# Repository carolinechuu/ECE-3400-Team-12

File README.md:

The home page is located in index.md, inside the master branch.

<!--
<div id="mySidenav" class="sidenav">
  <a href="javascript:void(0)" class="closebtn" onclick="closeNav()">&times;</a>
  <a href="#">About</a>
  <a href="#">Services</a>
  <a href="#">Clients</a>
  <a href="#">Contact</a>
</div> -->

<!--
<div class="w3-sidebar w3-bar-block" style="width:25%"> 
  <a href="#" class="w3-bar-item w3-button">Link 1</a>
  <a href="#" class="w3-bar-item w3-button">Link 2</a>
  <a href="#" class="w3-bar-item w3-button">Link 3</a>
</div>
-->

<!--<div style="margin-left:25%">-->

<!-- Use any element to open the sidenav 
<span onclick="openNav()">close</span>

-->

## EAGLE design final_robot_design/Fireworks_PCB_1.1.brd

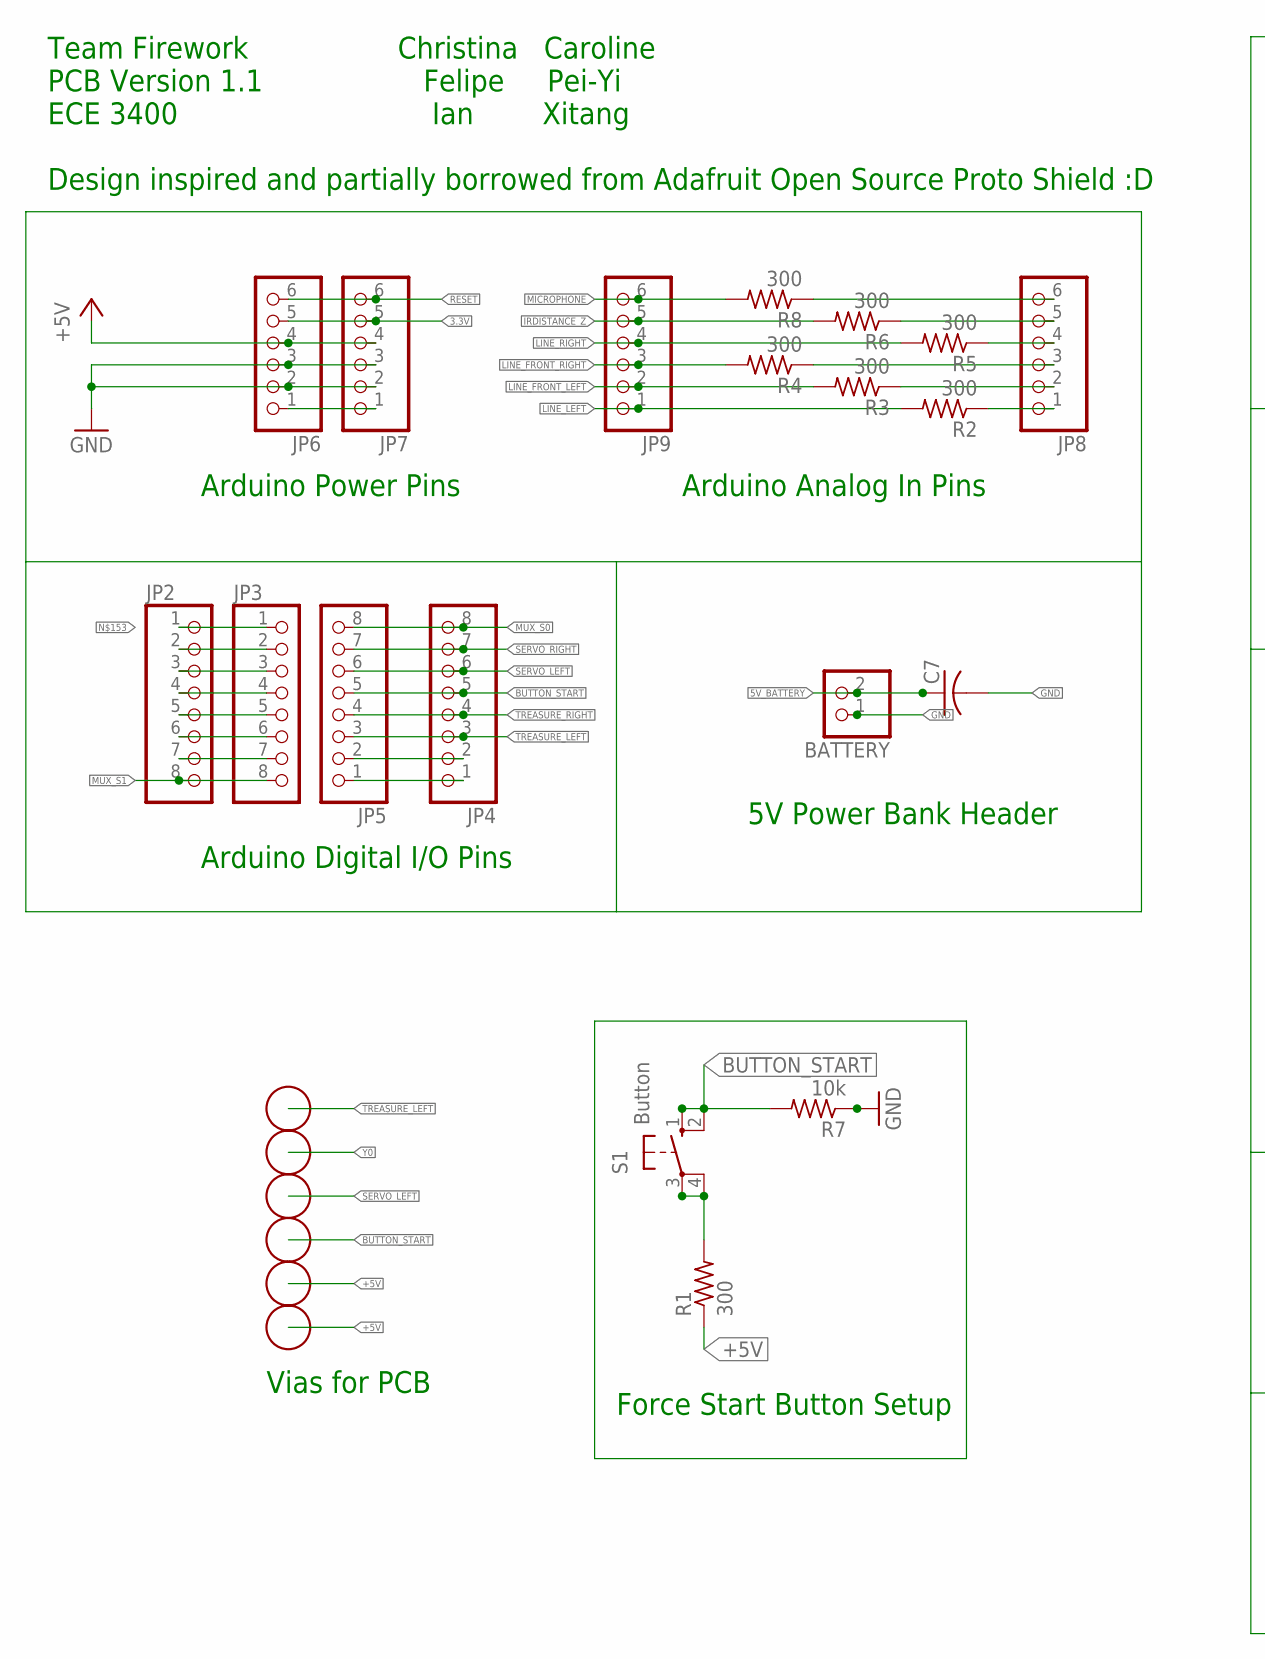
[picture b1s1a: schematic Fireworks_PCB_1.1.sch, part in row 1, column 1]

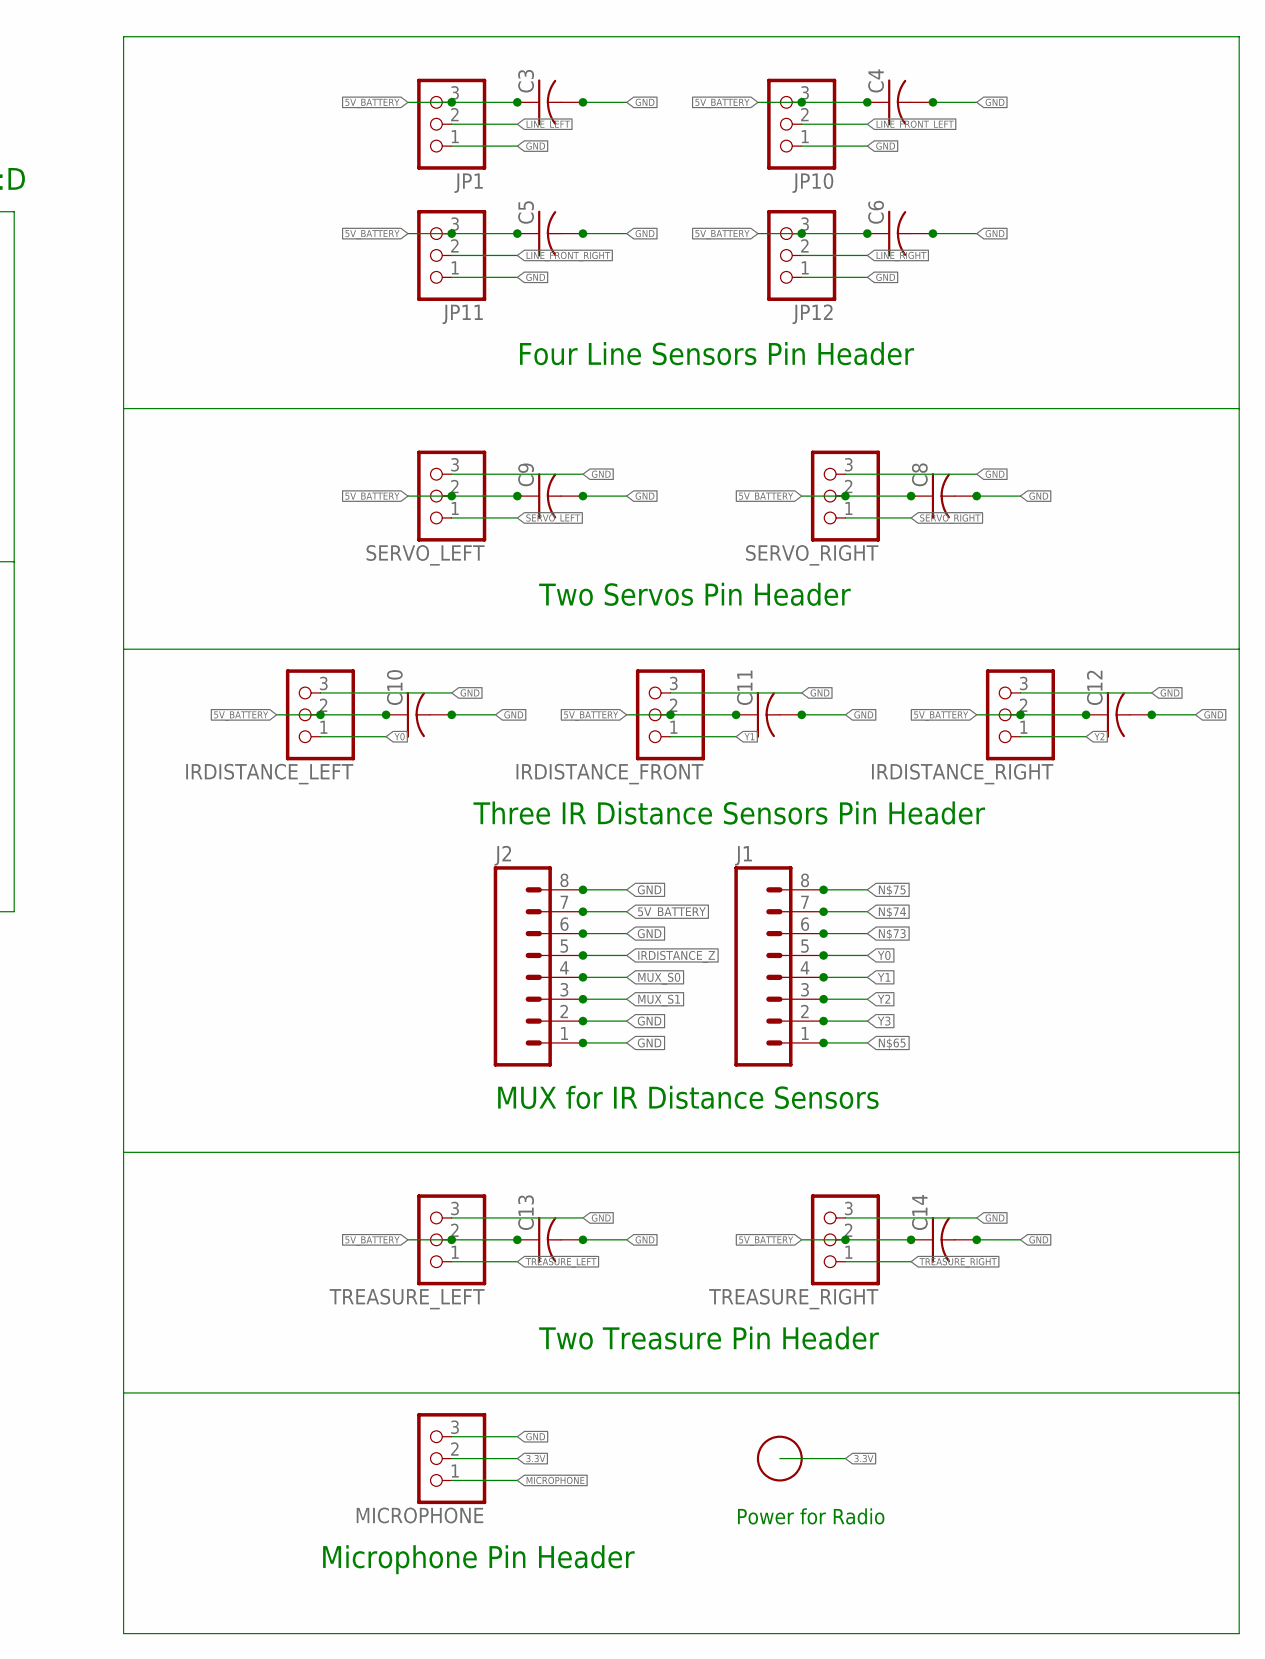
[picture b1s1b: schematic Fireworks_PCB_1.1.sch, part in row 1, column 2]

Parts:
BATTERY: PINHD-1X2; 1X02
C3, C4, C5, C6, C7, C8, C9, C10, C11, C12, C13, C14: C-US025-025X050; C025-025X050
IRDISTANCE_FRONT: PINHD-1X3; 1X03
IRDISTANCE_LEFT: PINHD-1X3; 1X03
IRDISTANCE_RIGHT: PINHD-1X3; 1X03
J1, J2: M08; 1X08_ROUND
JP1, JP10, JP11, JP12: PINHD-1X3; 1X03
JP2, JP4: PINHD-1X8B; 1X08-BIG
JP3, JP5: PINHD-1X8CLEANBIG; 1X08-CLEANBIG
JP6, JP8: PINHD-1X6CB; 1X06-CLEANBIG
JP7, JP9: PINHD-1X6B; 1X06-BIG
MICROPHONE: PINHD-1X3; 1X03
R1, R2, R3, R4, R5, R6, R8: 300; 0207/5V
R7: 10k; 0207/5V
S1: Button; B3F-10XX
SERVO_LEFT: PINHD-1X3; 1X03
SERVO_RIGHT: PINHD-1X3; 1X03
TREASURE_LEFT: PINHD-1X3; 1X03
TREASURE_RIGHT: PINHD-1X3; 1X03
U$1, U$2, U$3, U$4, U$5, U$6, U$23: PERF; PERFHOLE

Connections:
3.3V: JP6.5, JP7.5, MICROPHONE.2, U$23.P$1
5V_BATTERY: BATTERY.2, C3.1, C4.1, C5.1, C6.1, C7.1, C8.1, C9.1, C10.1, C11.1, C12.1, C13.1, C14.1, IRDISTANCE_FRONT.2, IRDISTANCE_LEFT.2, IRDISTANCE_RIGHT.2, J2.7, JP1.3, JP10.3, JP11.3, JP12.3, SERVO_LEFT.2, SERVO_RIGHT.2, TREASURE_LEFT.2, TREASURE_RIGHT.2
+5V: JP6.4, JP7.4, R1.1, U$4.P$1, U$5.P$1
BUTTON_START: JP4.5, JP5.5, R7.2, S1.1 (S), S1.2 (S1), U$3.P$1
GND: BATTERY.1, C3.2, C4.2, C5.2, C6.2, C7.2, C8.2, C9.2, C10.2, C11.2, C12.2, C13.2, C14.2, IRDISTANCE_FRONT.3, IRDISTANCE_LEFT.3, IRDISTANCE_RIGHT.3, J2.1, J2.2, J2.6, J2.8, JP1.1, JP6.2, JP6.3, JP7.2, JP7.3, JP10.1, JP11.1, JP12.1, MICROPHONE.3, R7.1, SERVO_LEFT.3, SERVO_RIGHT.3, TREASURE_LEFT.3, TREASURE_RIGHT.3
IRDISTANCE_Z: J2.5, JP9.5, R6.2
LINE_FRONT_LEFT: JP9.2, JP10.2, R3.2
LINE_FRONT_RIGHT: JP9.3, JP11.2, R4.2
LINE_LEFT: JP1.2, JP9.1, R2.2
LINE_RIGHT: JP9.4, JP12.2, R5.2
MICROPHONE: JP9.6, MICROPHONE.1, R8.2
MUX_S0: J2.4, JP4.8, JP5.8
MUX_S1: J2.3, JP2.8, JP3.8
unnamed: R1.2, S1.3, S1.4 (P1)
unnamed: JP2.3, JP3.3
unnamed: JP8.5, R6.1
unnamed: JP8.4, R5.1
unnamed: JP2.5, JP3.5
unnamed: JP8.3, R4.1
unnamed: JP6.1, JP7.1
unnamed: JP2.4, JP3.4
unnamed: JP2.2, JP3.2
unnamed: JP8.6, R8.1
unnamed: JP2.7, JP3.7
unnamed: JP2.6, JP3.6
unnamed: JP2.1, JP3.1
unnamed: JP8.1, R2.1
unnamed: JP8.2, R3.1
unnamed: JP4.1, JP5.1
unnamed: JP4.2, JP5.2
RESET: JP6.6, JP7.6
SERVO_LEFT: JP4.6, JP5.6, SERVO_LEFT.1, U$2.P$1
SERVO_RIGHT: JP4.7, JP5.7, SERVO_RIGHT.1
TREASURE_LEFT: JP4.3, JP5.3, TREASURE_LEFT.1, U$6.P$1
TREASURE_RIGHT: JP4.4, JP5.4, TREASURE_RIGHT.1
Y0: IRDISTANCE_LEFT.1, J1.5, U$1.P$1
Y1: IRDISTANCE_FRONT.1, J1.4
Y2: IRDISTANCE_RIGHT.1, J1.3
Y3: J1.2

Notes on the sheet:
Arduino Analog In Pins
Arduino Digital I/O Pins
MUX for IR Distance Sensors
Four Line Sensors Pin Header
Arduino Power Pins
5V Power Bank Header
Force Start Button Setup
Two Servos Pin Header
Three IR Distance Sensors Pin Header
Two Treasure Pin Header
Microphone Pin Header
Power for Radio
Vias for PCB
Team Firework PCB Version 1.1 ECE 3400
Christina Caroline Felipe Pei-Yi Ian Xitang
Design inspired and partially borrowed from Adafruit Open Source Proto Shield :D

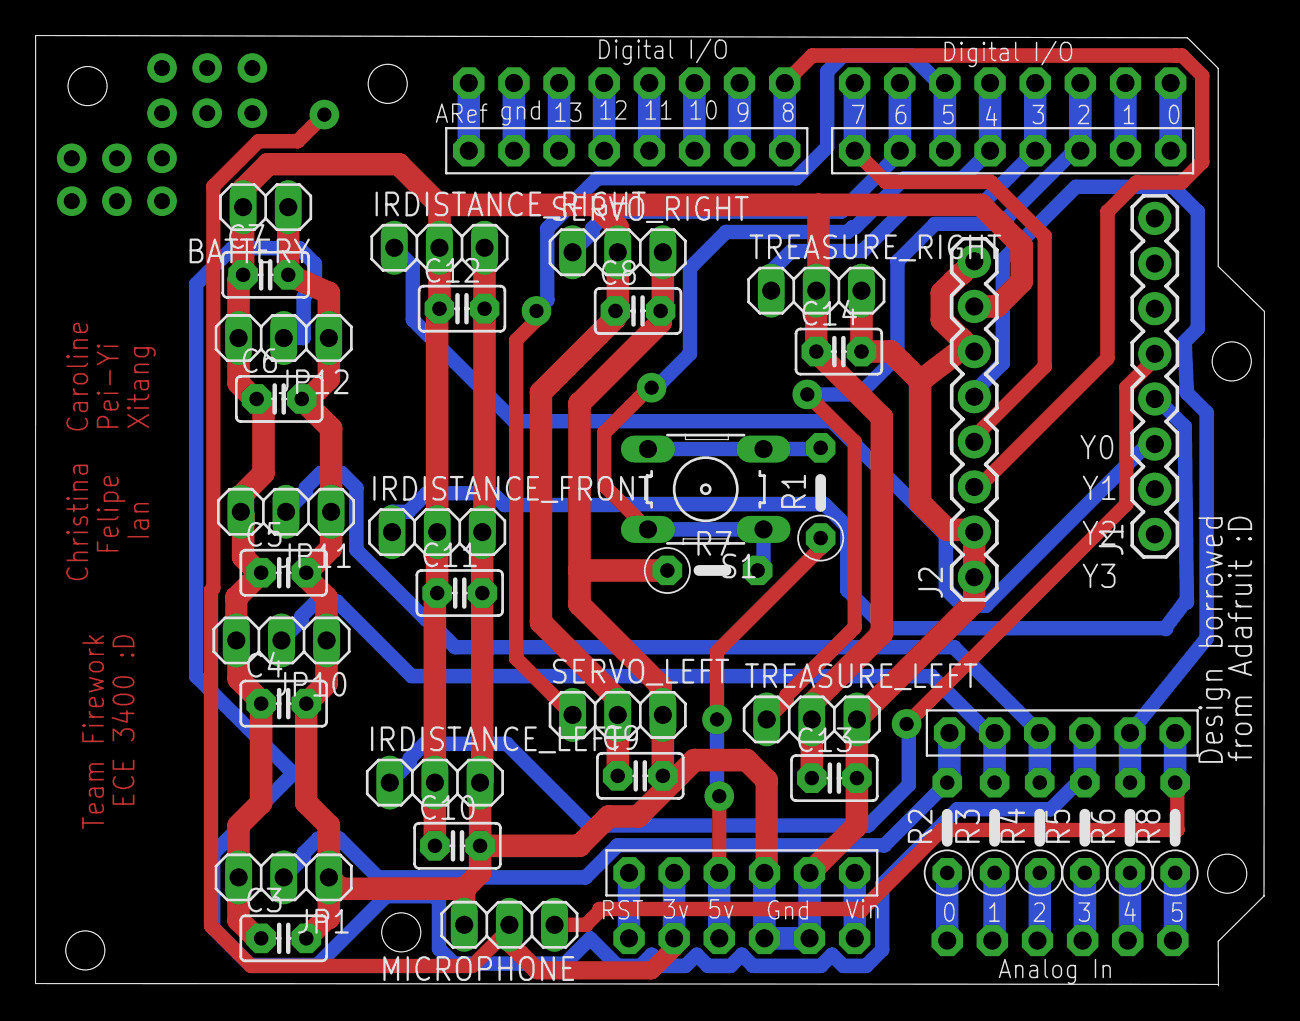
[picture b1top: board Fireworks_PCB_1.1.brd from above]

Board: 2 copper layers, 69.2 x 53.5 mm, 51 parts (0 on the bottom side), 38 nets.

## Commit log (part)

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2017-09-01 Update _config.yml
    Add baseurl
2017-09-01 Add team contract PDF
2017-09-01 Update about.md
    Add team contract PDF link
2017-09-01 Rename contract pdf
2017-09-01 Move all pages to master
2017-09-02 Cool rotation effect on all h1 font type
2017-09-02 Add github_local_setup.pdf
2017-09-02 Add dropdown navbar buttons
2017-09-04 Add firework.mp3
2017-09-04 Integrate audio in index.md
2017-09-04 Create lab1.md file
2017-09-04 Updated part 4 of lab1.md
2017-09-04 Nothing changed
2017-09-04 Commit message
2017-09-05 Update folders and lab 1 link
2017-09-05 Put up lab 1 media
2017-09-05 Update code block ticks
2017-09-05 Update reference to CSS
2017-09-05 changed css ref link
2017-09-05 trying to fix the navbar
2017-09-05 fixed navbar
2017-09-05 navbar links fix attempt
2017-09-06 Create a new line for mini project 3 from image
2017-09-06 Part 5, Servo duty cycle, oscilloscope stuffs
2017-09-06 spacing issues
2017-09-06 Part 5 format issues
2017-09-06 Trying to fix line space format issue
2017-09-06 Trying to fix part 5 space issue attempt 2
2017-09-06 Part 5 servo max/min duty cycle comment
2017-09-06 Add datasheet link
2017-09-06 robot.h code uploaded
2017-09-06 main code uploaded and comments
2017-09-06 Soldering Pictures
2017-09-06 picture bug fixed
2017-09-06 fireworkBackground.gif
2017-09-06 Change background image to fireworks
2017-09-07 Update lab1.md
    Add language tags to code blocks
2017-09-07 Crop some pictures
2017-09-07 Update lab1.md
    Tables for certain images
2017-09-07 Fixed Lab1 Part3 CodeOutput Picture
2017-09-07 emoji
2017-09-08 Create does_not_exist
2017-09-08 Rename does_not_exist to does_not_exist.md
2017-09-13 Update lab2.md
    Add navbar
2017-09-13 Added prelab to Lab2
2017-09-18 Update color scheme
2017-09-18 Add milestone1 page
2017-09-18 Add milestone1 link
2017-09-18 Testing dropdown buttons
2017-09-18 Take out dropbuttons
2017-09-18 Acoustic Team
2017-09-18 Add Figure 1
2017-09-18 add !
2017-09-18 add table
2017-09-18 fix figure 1
2017-09-18 fix pic
2017-09-18 change color
2017-09-18 add color
2017-09-18 change css
2017-09-18 add another table
2017-09-18 put table in correct space
2017-09-18 add pic
2017-09-19 erase table
2017-09-19 change to purple
2017-09-19 change header
2017-09-19 change to black
2017-09-19 remove semicolon
2017-09-19 add amp pic
2017-09-20 Finish prelab FFT stuff
2017-09-20 Fix LaTeX equation
2017-09-20 Edit at the beginning
2017-09-20 Make components into list
2017-09-20 Added FFT analysis
2017-09-20 FFT analysis and amplifier circuit discussion.
2017-09-20 opamp stuff
2017-09-20 Add fireworks animation
2017-09-20 Op Amp stuffs
2017-09-21 More acoustics stuffs
2017-09-21 Acoustics update
2017-09-21 acoustics updatesss
2017-09-21 gramma
2017-09-21 acousticscircuit.jpg
2017-09-21 image of the circuit added for accoustics
2017-09-21 test Per-Yi's firework javascript
2017-09-21 test
2017-09-21 test3
2017-09-21 test 3
2017-09-21 test 4
2017-09-21 test 5
2017-09-21 test6
2017-09-21 test7
2017-09-21 test 8
2017-09-21 add pics for optics
2017-09-21 add infrared circuit
2017-09-21 add optics3
2017-09-21 add more to ir
2017-09-21 finish optics
2017-09-21 Fixed link in milestone 1
2017-09-21 Fixed more links in Milestone 1
2017-09-21 center video
2017-09-21 video
2017-09-22 Add slideshow
2017-09-22 Add slideshow pictures
2017-09-22 Edit slideshow pictures
2017-09-22 Change to automatic slideshow
2017-09-22 Change carousel time
2017-09-22 Add slideshow animation
2017-09-22 Edit slideshow animation
2017-09-22 Edit index.md
2017-09-22 Change h1 color
2017-09-22 Edit fireworks
2017-09-22 Edit fireworks canvas
2017-09-22 Edit fireworks dimensions
2017-09-22 Edit firework window
2017-09-22 Edit fireworks window
2017-09-29 Add milestone 2 video
2017-09-29 Add milestone 2 link
2017-10-13 Add lab3.md
2017-10-13 Some acoustics team info
2017-10-13 Add wave images
2017-10-16 edited triangular and sawtooth typos
2017-10-16 modified square wave section
2017-10-16 Add extra to triangular/sawtooth wave section
2017-10-16 changed picture names lab3
2017-10-18 VGA team
2017-10-19 add break
2017-10-19 add pics
2017-10-19 add more pics
2017-10-19 readjust
2017-10-19 Add square wave pic and minor edits
2017-10-19 Edit table headers
2017-10-19 Add wirint_acoustics.jpg
2017-10-19 update FPGA descrition
2017-10-19 new image
2017-10-19 add c script
2017-10-19 upload code
2017-10-19 VGACircuit
2017-10-19 new VGA Circuit
2017-10-19 Lab 3 Arduino FPGA description
2017-10-19 VGA Circuit
2017-10-19 lab4
2017-10-19 lab 4 prelab
2017-10-19 lab 4 added
2017-10-25 WEBSITE 2.0!
2017-10-25 Added all pages
2017-10-25 Deleted some old files
2017-10-25 Minor updates
2017-10-25 Update links
2017-10-26 Lab 4 report
2017-10-26 receive.png
2017-10-27 lab 4 description update
2017-10-27 receive2.png
2017-10-27 lab4 description update
2017-10-27 code fixed done
2017-10-27 change
2017-10-27 lab 4 done
2017-10-27 done
2017-10-30 Update milestone1
2017-11-09 Update milestone 3
2017-11-10 added simulator/sim description
2017-11-10 made sim link work
2017-11-10 Update milestone3
2017-11-10 Video desc
2017-11-10 Edited some typos
2017-11-10 did the vid
2017-11-21 Update milestone 4
2017-11-21 Update milestone 4 page
2017-11-22 added to milestone 4
2017-11-22 did some milestone 4
2017-12-02 Update website
2017-12-03 Added DFS optimization to competition page
2017-12-03 HTML Tutorial still in progress
2017-12-03 Numerous small updates
2017-12-03 Navbar updates
2017-12-03 Add sparky.html
2017-12-03 Add competition timer
2017-12-03 small updates
2017-12-04 started css tutorial
2017-12-04 Updated image carousel
2017-12-05 Finished CSS tutorial, added bootstrap tutorial
2017-12-05 Bootstrap tutorial
2017-12-05 minor updates to tutorials
2017-12-06 new files
2017-12-06 new update
2017-12-06 PCB files
2017-12-06 power analysis
2017-12-06 new file
2017-12-06 Treasure png
2017-12-06 upload
2017-12-06 !important
2017-12-06 work plz
2017-12-06 lmao
2017-12-06 Index update
2017-12-06 fix?
2017-12-06 fix bug
2017-12-06 dope
2017-12-06 EB7070
2017-12-06 whatever
2017-12-06 bug fix hopefuflly
2017-12-06 Formatting fixes
2017-12-06 change back
2017-12-06 back to blue
2017-12-06 Fixing formatting
2017-12-06 Update competition page
2017-12-06 Finished tutorials and added to home page
2017-12-06 Added milestone 2 from md file
2017-12-06 Fixed index.html
2017-12-06 Open-sourced code
2017-12-06 Small fixes
2017-12-06 Small formatting fixes
2017-12-06 Link fix
2017-12-06 Add Bootstrap tutorial link
2017-12-07 pic bug fixed

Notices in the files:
parts and their libraries:
SparkFun-Connectors: Licensing: Creative Commons ShareAlike 4.0 International - https://creativecommons.org/licenses/by-sa/4.0
